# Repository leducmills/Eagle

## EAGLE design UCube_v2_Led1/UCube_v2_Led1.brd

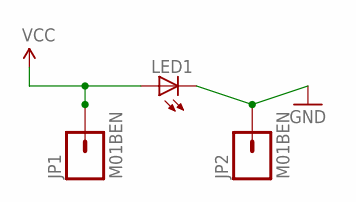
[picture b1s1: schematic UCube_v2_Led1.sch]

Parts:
JP1, JP2: M01BEN; 1X01-BEN
LED1: LED5MM

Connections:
GND: JP2.1, LED1.K (C)
VCC: JP1.1, LED1.A

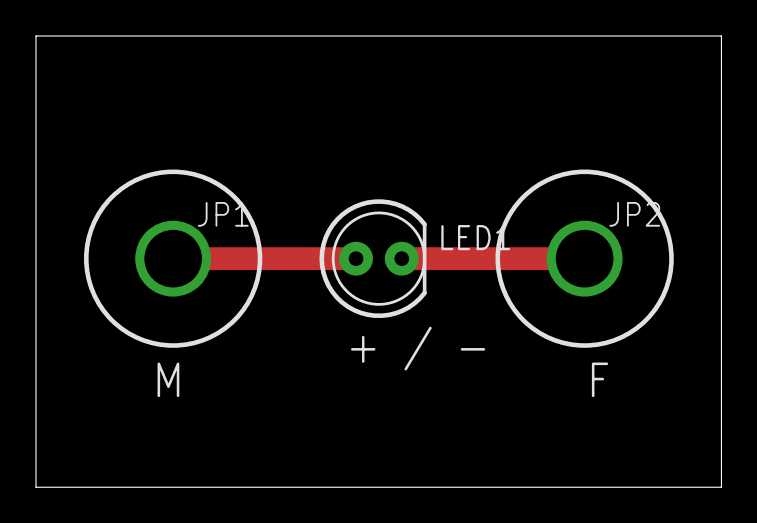
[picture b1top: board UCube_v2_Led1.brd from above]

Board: 2 copper layers, 38.1 x 25.1 mm, 3 parts (0 on the bottom side), 2 nets.

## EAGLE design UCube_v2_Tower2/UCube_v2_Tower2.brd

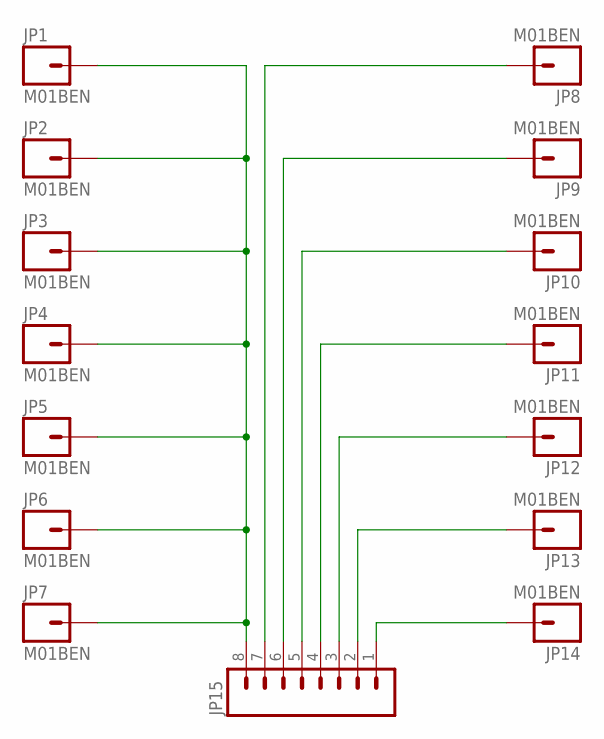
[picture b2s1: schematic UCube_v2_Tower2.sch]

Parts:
JP1, JP2, JP3, JP4, JP5, JP6, JP7, JP8, JP9, JP10, JP11, JP12, JP13, JP14: M01BEN; 1X01-BEN
JP15: M081X08; 1X08

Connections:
unnamed: JP1.1, JP2.1, JP3.1, JP4.1, JP5.1, JP6.1, JP7.1, JP15.8
unnamed: JP8.1, JP15.7
unnamed: JP9.1, JP15.6
unnamed: JP10.1, JP15.5
unnamed: JP11.1, JP15.4
unnamed: JP12.1, JP15.3
unnamed: JP13.1, JP15.2
unnamed: JP14.1, JP15.1

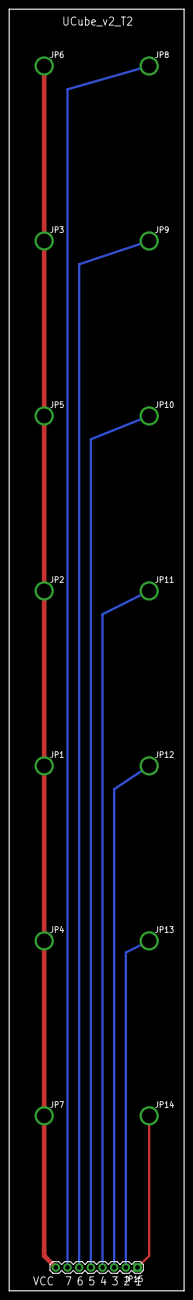
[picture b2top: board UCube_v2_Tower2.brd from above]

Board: 2 copper layers, 38.1 x 279.1 mm, 15 parts (0 on the bottom side), 8 nets.

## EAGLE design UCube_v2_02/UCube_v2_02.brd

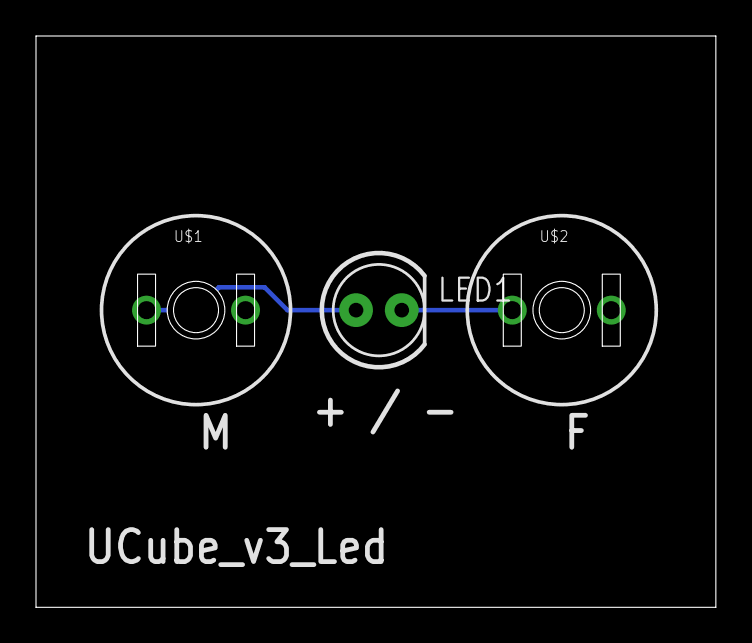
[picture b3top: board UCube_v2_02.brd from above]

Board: 2 copper layers, 37.8 x 31.7 mm, 3 parts (0 on the bottom side), 2 nets.

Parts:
LED1: LED5MM
U$1, U$2: BUTTON-MAGNETIC10MM; BUTTON-10MM

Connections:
GND: LED1.K, U$2.1
VCC: LED1.A, U$1.1

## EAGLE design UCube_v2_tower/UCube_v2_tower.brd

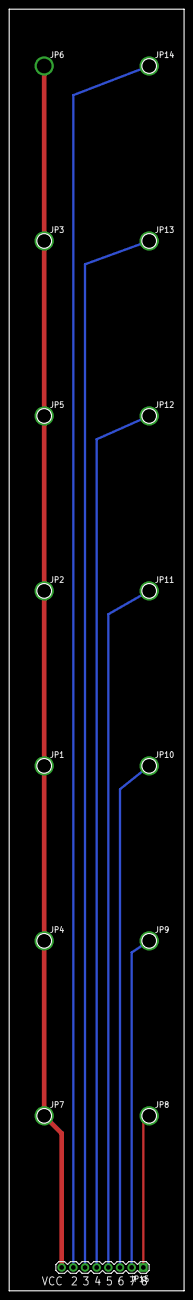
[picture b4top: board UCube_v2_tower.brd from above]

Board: 2 copper layers, 38.1 x 279.1 mm, 15 parts (0 on the bottom side), 8 nets.

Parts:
JP1, JP2, JP3, JP4, JP5, JP7, JP8, JP9, JP10, JP11, JP12, JP13, JP14: M01PTH; 1X01-BEN
JP6: M01BEN; 1X01-BEN
JP15: 1X08

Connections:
unnamed: JP8.1, JP15.1
unnamed: JP9.1, JP15.2
unnamed: JP10.1, JP15.3
unnamed: JP11.1, JP15.4
unnamed: JP12.1, JP15.5
unnamed: JP13.1, JP15.6
unnamed: JP14.1, JP15.7
VCC: JP1.1, JP2.1, JP3.1, JP4.1, JP5.1, JP6.1, JP7.1, JP15.8

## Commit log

2013-02-08 Eagle
    Circuit designs and schematics

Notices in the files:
parts and their libraries:
SparkFun: Licensing: CC v3.0 Share-Alike You are welcome to use this library for commercial purposes.
